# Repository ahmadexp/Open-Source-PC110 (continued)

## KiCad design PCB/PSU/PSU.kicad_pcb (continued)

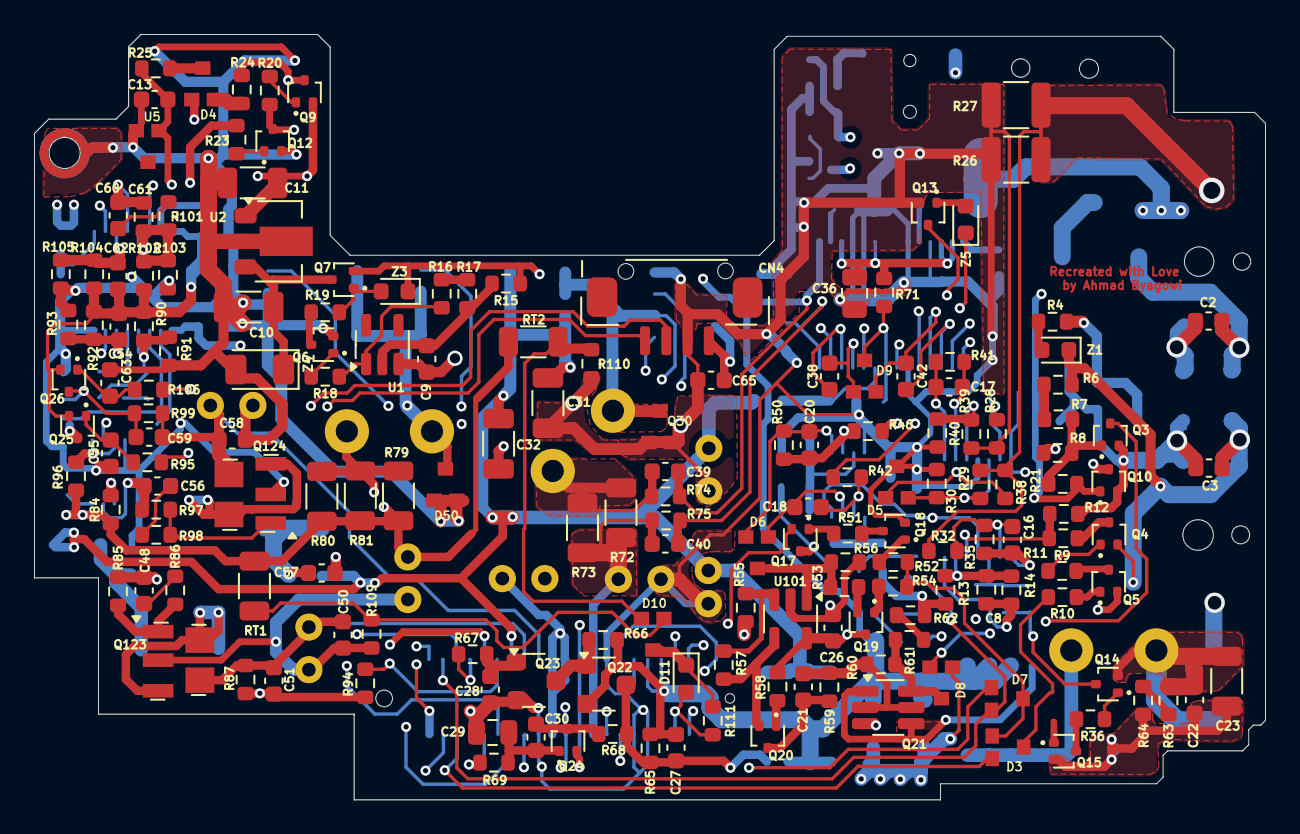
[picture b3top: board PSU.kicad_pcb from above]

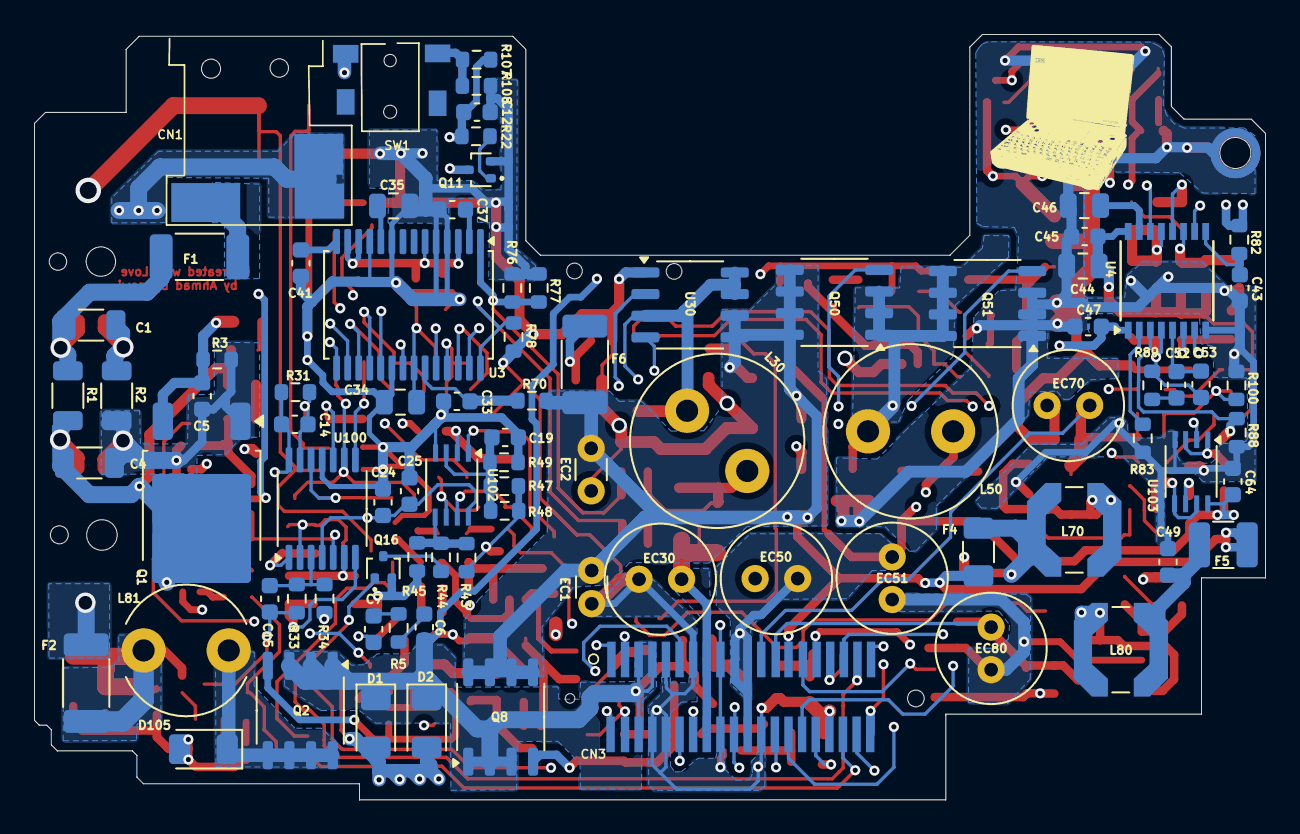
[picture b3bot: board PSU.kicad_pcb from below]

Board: 4 copper layers, 72.3 x 45.0 mm, 257 parts (87 on the bottom side), 154 nets.

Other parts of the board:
G1: LOGO; logo

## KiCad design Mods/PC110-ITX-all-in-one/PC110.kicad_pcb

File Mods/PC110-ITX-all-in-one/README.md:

## PC110-ITX all-in-one

This is an effort to build an ITX form factor motherboard with all the PC110 components, the docking station as the PSU board all blended.

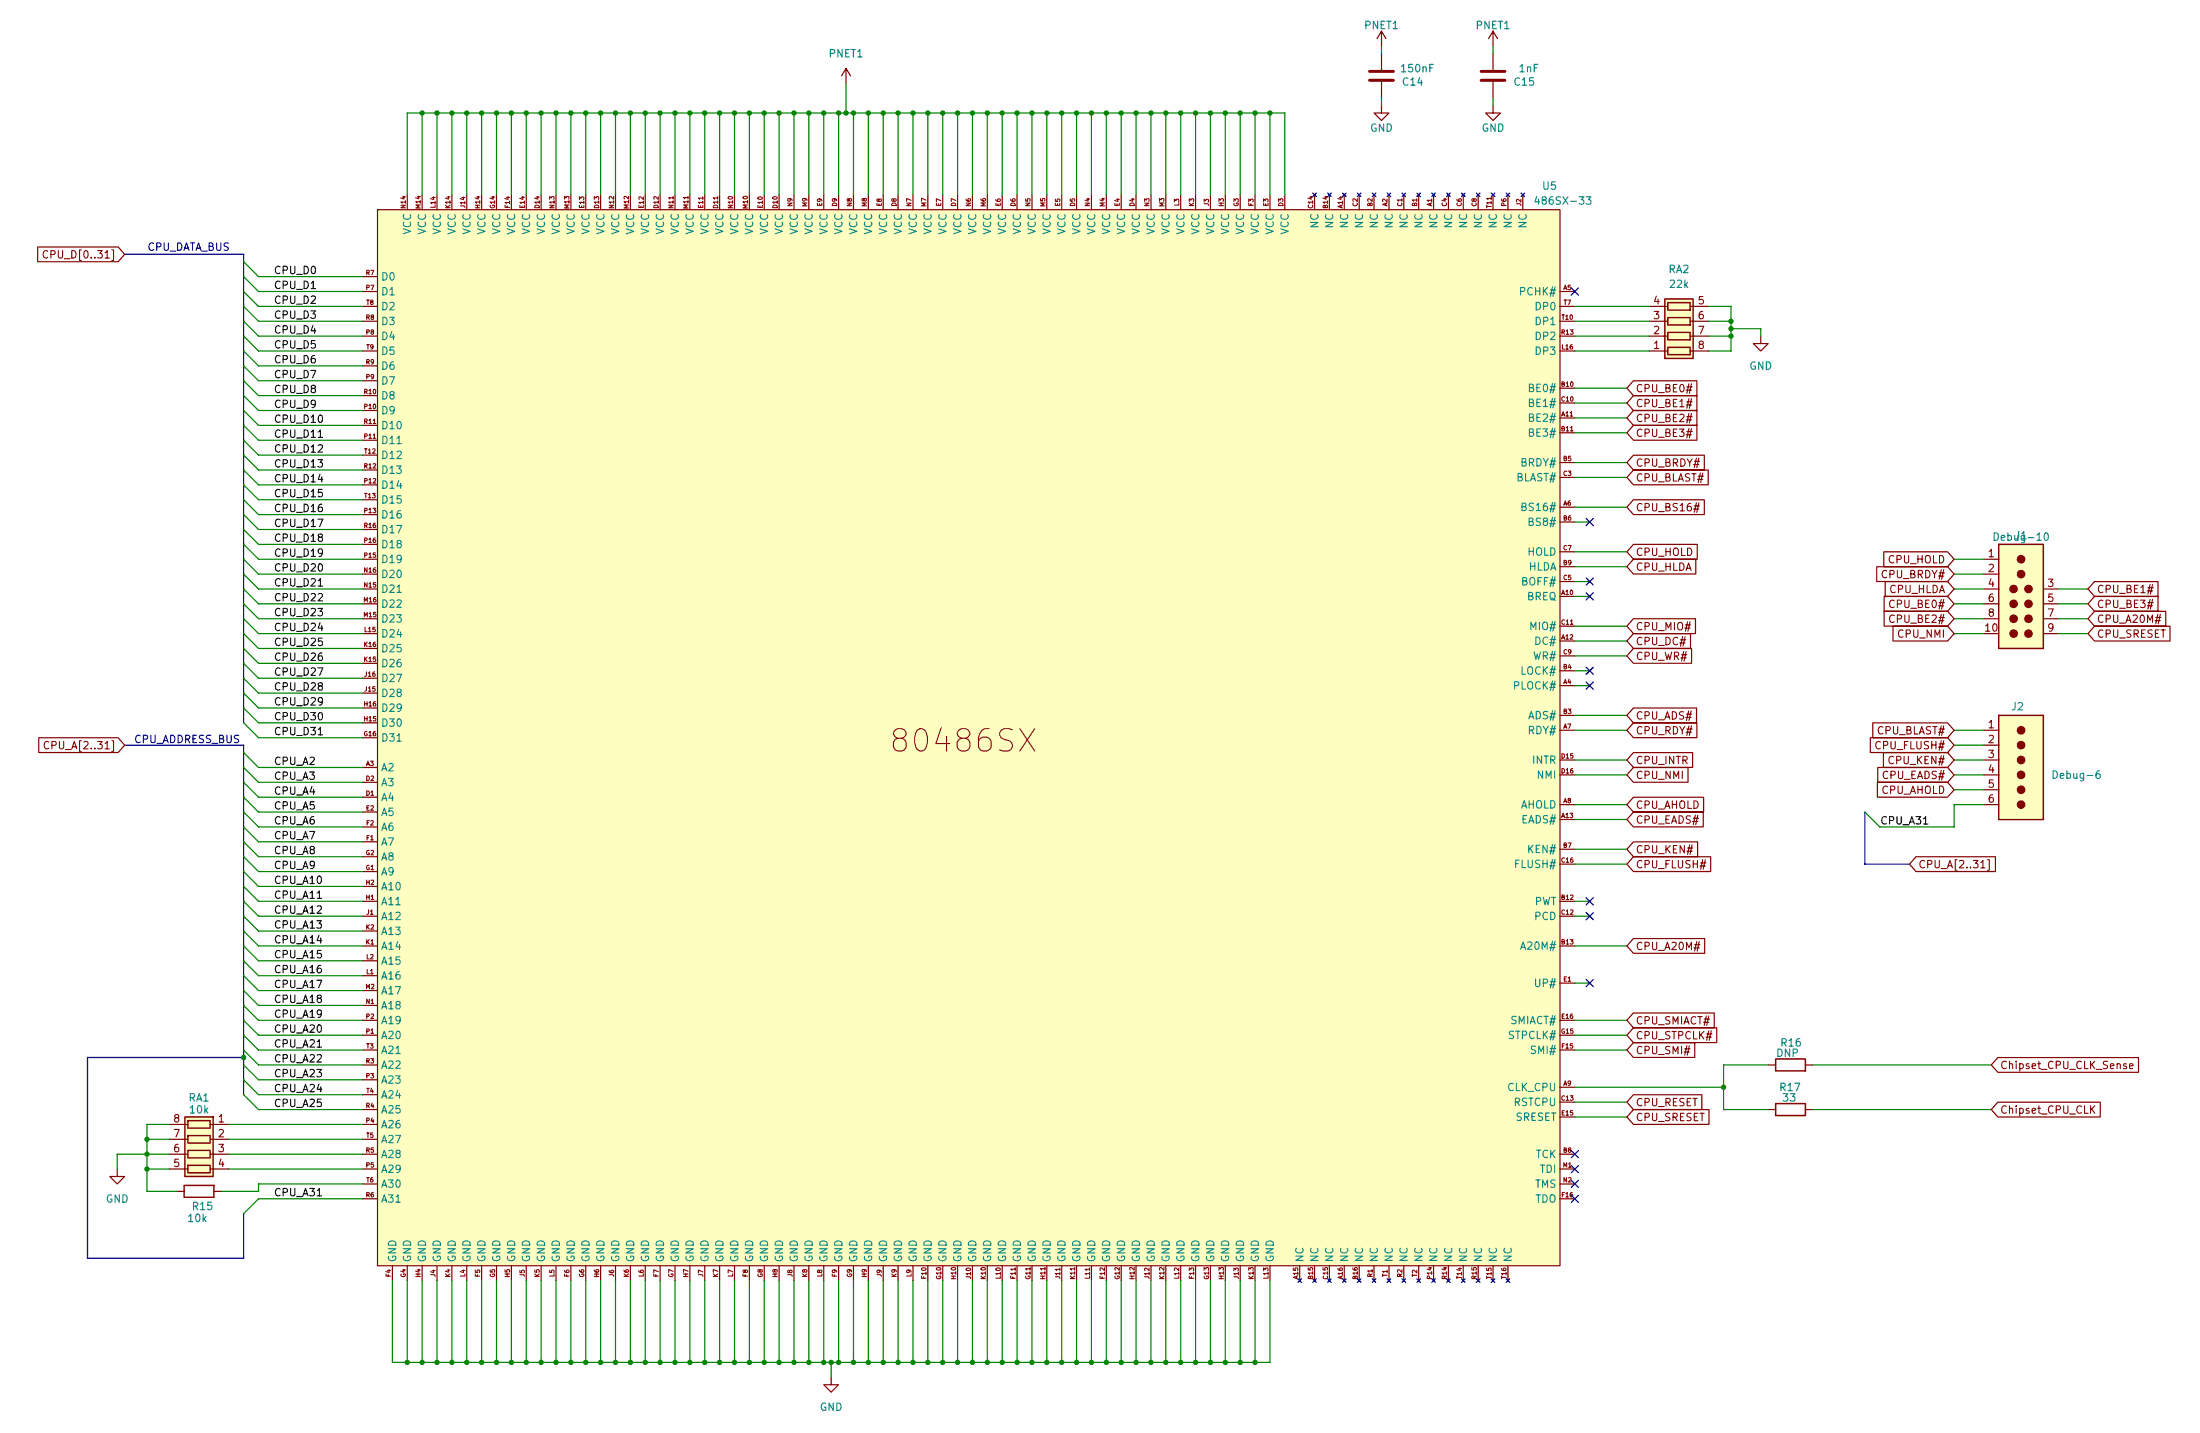
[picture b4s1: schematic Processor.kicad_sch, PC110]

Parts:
C14: 150nF; C_0402_1005Metric
C15: 1nF; C_0402_1005Metric
J1: Debug-10
J2: Debug-6
R15: 10k; R_0402_1005Metric
R16: DNP; R_0402_1005Metric
R17: 33; R_0402_1005Metric
RA1: 10k; R-array
RA2: 22k; R-array
U5: 486SX-33; BGA-256

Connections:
CPU_A2: U5.A3 (A2); also elsewhere on the board
CPU_A3: U5.D2 (A3); also elsewhere on the board
CPU_A4: U5.D1 (A4); also elsewhere on the board
CPU_A5: U5.E2 (A5); also elsewhere on the board
CPU_A6: U5.F2 (A6); also elsewhere on the board
CPU_A7: U5.F1 (A7); also elsewhere on the board
CPU_A8: U5.G2 (A8); also elsewhere on the board
CPU_A9: U5.G1 (A9); also elsewhere on the board
CPU_A10: U5.H2 (A10); also elsewhere on the board
CPU_A11: U5.H1 (A11); also elsewhere on the board
CPU_A12: U5.J1 (A12); also elsewhere on the board
CPU_A13: U5.K2 (A13); also elsewhere on the board
CPU_A14: U5.K1 (A14); also elsewhere on the board
CPU_A15: U5.L2 (A15); also elsewhere on the board
CPU_A16: U5.L1 (A16); also elsewhere on the board
CPU_A17: U5.M2 (A17); also elsewhere on the board
CPU_A18: U5.N1 (A18); also elsewhere on the board
CPU_A19: U5.P2 (A19); also elsewhere on the board
CPU_A20: U5.P1 (A20); also elsewhere on the board
CPU_A20M#: J1.7, U5.B13 (A20M#); also elsewhere on the board
CPU_A21: U5.T3 (A21); also elsewhere on the board
CPU_A22: U5.R3 (A22); also elsewhere on the board
CPU_A23: U5.P3 (A23); also elsewhere on the board
CPU_A24: U5.T4 (A24); also elsewhere on the board
CPU_A25: U5.R4 (A25); also elsewhere on the board
CPU_A31: J2.6, U5.R6 (A31); also elsewhere on the board
CPU_ADS#: U5.B3 (ADS#); also elsewhere on the board
CPU_AHOLD: J2.5, U5.A8 (AHOLD); also elsewhere on the board
CPU_BE0#: J1.6, U5.B10 (BE0#); also elsewhere on the board
CPU_BE1#: J1.3, U5.C10 (BE1#); also elsewhere on the board
CPU_BE2#: J1.8, U5.A11 (BE2#); also elsewhere on the board
CPU_BE3#: J1.5, U5.B11 (BE3#); also elsewhere on the board
CPU_BLAST#: J2.1, U5.C3 (BLAST#); also elsewhere on the board
CPU_BRDY#: J1.2, U5.B5 (BRDY#); also elsewhere on the board
CPU_BS16#: U5.A6 (BS16#); also elsewhere on the board
CPU_D0: U5.R7 (D0); also elsewhere on the board
CPU_D1: U5.P7 (D1); also elsewhere on the board
CPU_D2: U5.T8 (D2); also elsewhere on the board
CPU_D3: U5.R8 (D3); also elsewhere on the board
CPU_D4: U5.P8 (D4); also elsewhere on the board
CPU_D5: U5.T9 (D5); also elsewhere on the board
CPU_D6: U5.R9 (D6); also elsewhere on the board
CPU_D7: U5.P9 (D7); also elsewhere on the board
CPU_D8: U5.R10 (D8); also elsewhere on the board
CPU_D9: U5.P10 (D9); also elsewhere on the board
CPU_D10: U5.R11 (D10); also elsewhere on the board
CPU_D11: U5.P11 (D11); also elsewhere on the board
CPU_D12: U5.T12 (D12); also elsewhere on the board
CPU_D13: U5.R12 (D13); also elsewhere on the board
CPU_D14: U5.P12 (D14); also elsewhere on the board
CPU_D15: U5.T13 (D15); also elsewhere on the board
CPU_D16: U5.P13 (D16); also elsewhere on the board
CPU_D17: U5.R16 (D17); also elsewhere on the board
CPU_D18: U5.P16 (D18); also elsewhere on the board
CPU_D19: U5.P15 (D19); also elsewhere on the board
CPU_D20: U5.N16 (D20); also elsewhere on the board
CPU_D21: U5.N15 (D21); also elsewhere on the board
CPU_D22: U5.M16 (D22); also elsewhere on the board
CPU_D23: U5.M15 (D23); also elsewhere on the board
CPU_D24: U5.L15 (D24); also elsewhere on the board
CPU_D25: U5.K16 (D25); also elsewhere on the board
CPU_D26: U5.K15 (D26); also elsewhere on the board
CPU_D27: U5.J16 (D27); also elsewhere on the board
CPU_D28: U5.J15 (D28); also elsewhere on the board
CPU_D29: U5.H16 (D29); also elsewhere on the board
CPU_D30: U5.H15 (D30); also elsewhere on the board
CPU_D31: U5.G16 (D31); also elsewhere on the board
CPU_DC#: U5.A12 (DC#); also elsewhere on the board
CPU_EADS#: J2.4, U5.A13 (EADS#); also elsewhere on the board
CPU_FLUSH#: J2.2, U5.C16 (FLUSH#); also elsewhere on the board
CPU_HLDA: J1.4, U5.B9 (HLDA); also elsewhere on the board
CPU_HOLD: J1.1, U5.C7 (HOLD); also elsewhere on the board
CPU_INTR: U5.D15 (INTR); also elsewhere on the board
CPU_KEN#: J2.3, U5.B7 (KEN#); also elsewhere on the board
CPU_MIO#: U5.C11 (MIO#); also elsewhere on the board
CPU_NMI: J1.10, U5.D16 (NMI); also elsewhere on the board
CPU_RDY#: U5.A7 (RDY#); also elsewhere on the board
CPU_RESET: U5.C13 (RSTCPU); also elsewhere on the board
CPU_SMI#: U5.F15 (SMI#); also elsewhere on the board
CPU_SMIACT#: U5.E16 (SMIACT#); also elsewhere on the board
CPU_SRESET: J1.9, U5.E15 (SRESET); also elsewhere on the board
CPU_STPCLK#: U5.G15 (STPCLK#); also elsewhere on the board
CPU_WR#: U5.C9 (WR#); also elsewhere on the board
Chipset_CPU_CLK: R17.1; also elsewhere on the board
Chipset_CPU_CLK_Sense: R16.2; also elsewhere on the board
GND: C14.1, C15.1, R15.1, RA1.5 (R4.2), RA1.6 (R3.2), RA1.7 (R2.2), RA1.8 (R1.2), RA2.5 (R4.2), RA2.6 (R3.2), RA2.7 (R2.2), RA2.8 (R1.2), U5.F4 (GND), U5.F5 (GND), U5.F6 (GND), U5.F7 (GND), U5.F8 (GND), U5.F9 (GND), U5.F10 (GND), U5.F11 (GND), U5.F12 (GND), U5.F13 (GND), U5.G4 (GND), U5.G5 (GND), U5.G6 (GND), U5.G7 (GND), U5.G8 (GND), U5.G9 (GND), U5.G10 (GND), U5.G11 (GND), U5.G12 (GND), U5.G13 (GND), U5.H4 (GND), U5.H5 (GND), U5.H6 (GND), U5.H7 (GND), U5.H8 (GND), U5.H9 (GND), U5.H10 (GND), U5.H11 (GND), U5.H12 (GND), U5.H13 (GND), U5.J4 (GND), U5.J5 (GND), U5.J6 (GND), U5.J7 (GND), U5.J8 (GND), U5.J9 (GND), U5.J10 (GND), U5.J11 (GND), U5.J12 (GND), U5.J13 (GND), U5.K4 (GND), U5.K5 (GND), U5.K6 (GND), U5.K7 (GND), U5.K8 (GND), U5.K9 (GND), U5.K10 (GND), U5.K11 (GND), U5.K12 (GND), U5.K13 (GND), U5.L4 (GND), U5.L5 (GND), U5.L6 (GND), U5.L7 (GND), U5.L8 (GND), U5.L9 (GND), U5.L10 (GND), U5.L11 (GND), U5.L12 (GND), U5.L13 (GND); also elsewhere on the board
unnamed: RA1.1 (R1.1), U5.P4 (A26)
unnamed: RA1.2 (R2.1), U5.T5 (A27)
unnamed: RA1.3 (R3.1), U5.R5 (A28)
unnamed: RA1.4 (R4.1), U5.P5 (A29)
unnamed: RA2.1 (R1.1), U5.L16 (DP3)
unnamed: RA2.2 (R2.1), U5.R13 (DP2)
unnamed: RA2.3 (R3.1), U5.T10 (DP1)
unnamed: RA2.4 (R4.1), U5.T7 (DP0)
unnamed: R15.2, U5.T6 (A30)
unnamed: R16.1, R17.2, U5.A9 (CLK_CPU)
PNET1: C14.2, C15.2, U5.D3 (VCC), U5.D4 (VCC), U5.D5 (VCC), U5.D6 (VCC), U5.D7 (VCC), U5.D8 (VCC), U5.D9 (VCC), U5.D10 (VCC), U5.D11 (VCC), U5.D12 (VCC), U5.D13 (VCC), U5.D14 (VCC), U5.E3 (VCC), U5.E4 (VCC), U5.E5 (VCC), U5.E6 (VCC), U5.E7 (VCC), U5.E8 (VCC), U5.E9 (VCC), U5.E10 (VCC), U5.E11 (VCC), U5.E12 (VCC), U5.E13 (VCC), U5.E14 (VCC), U5.F3 (VCC), U5.F14 (VCC), U5.G3 (VCC), U5.G14 (VCC), U5.H3 (VCC), U5.H14 (VCC), U5.J3 (VCC), U5.J14 (VCC), U5.K3 (VCC), U5.K14 (VCC), U5.L3 (VCC), U5.L14 (VCC), U5.M3 (VCC), U5.M4 (VCC), U5.M5 (VCC), U5.M6 (VCC), U5.M7 (VCC), U5.M8 (VCC), U5.M9 (VCC), U5.M10 (VCC), U5.M11 (VCC), U5.M12 (VCC), U5.M13 (VCC), U5.M14 (VCC), U5.N3 (VCC), U5.N4 (VCC), U5.N5 (VCC), U5.N6 (VCC), U5.N7 (VCC), U5.N8 (VCC), U5.N9 (VCC), U5.N10 (VCC), U5.N11 (VCC), U5.N12 (VCC), U5.N13 (VCC), U5.N14 (VCC); also elsewhere on the board

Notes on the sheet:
CPU_ADDRESS_BUS
CPU_DATA_BUS
